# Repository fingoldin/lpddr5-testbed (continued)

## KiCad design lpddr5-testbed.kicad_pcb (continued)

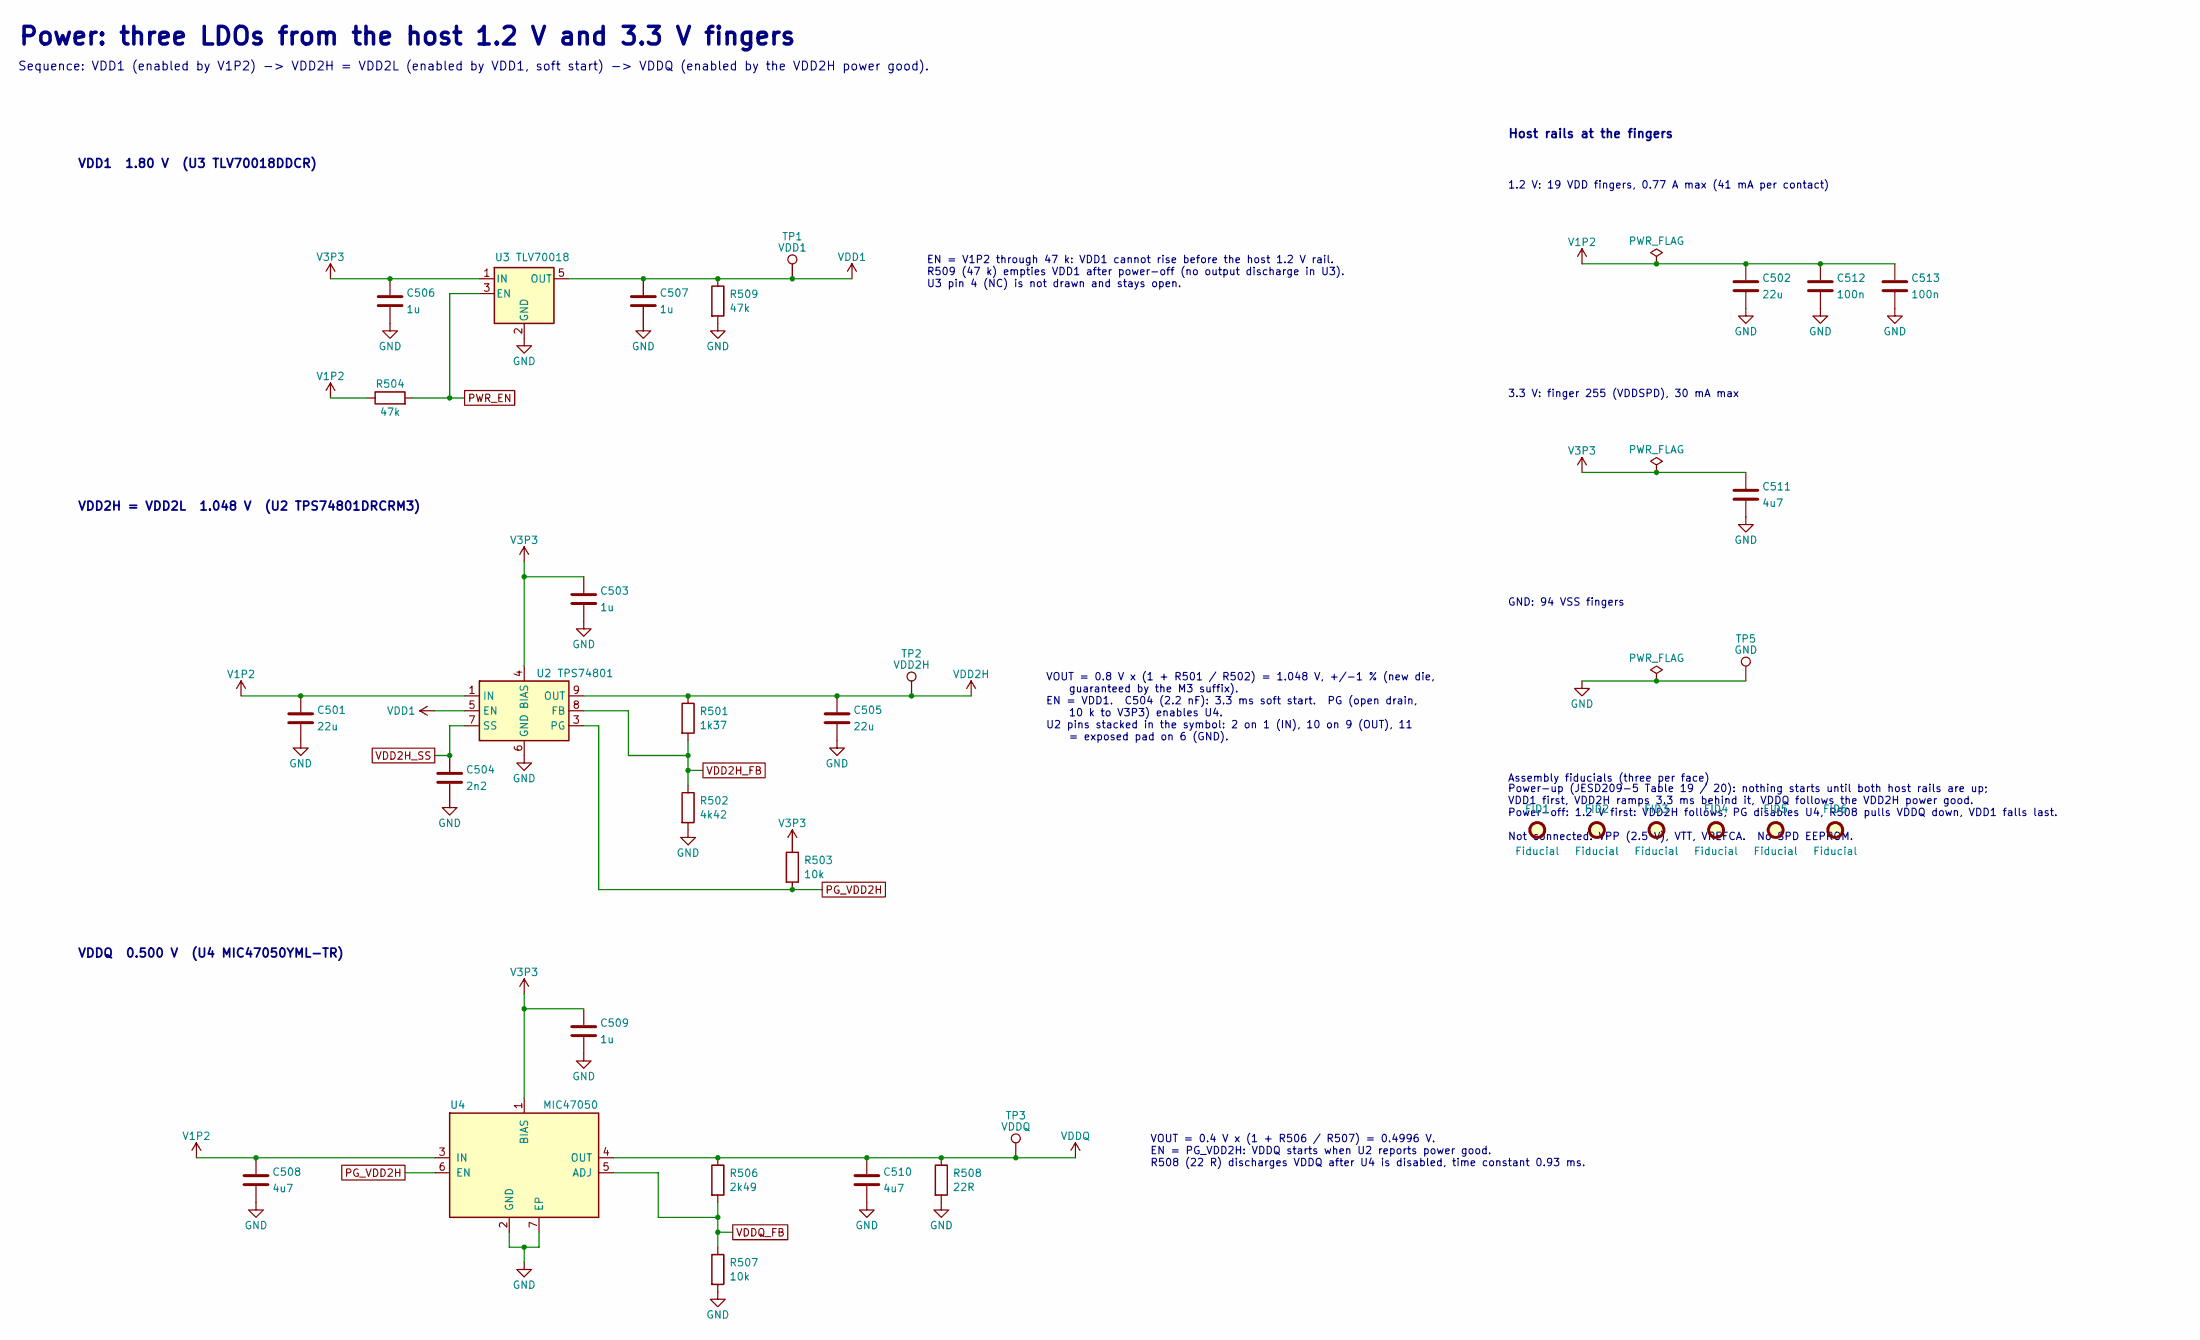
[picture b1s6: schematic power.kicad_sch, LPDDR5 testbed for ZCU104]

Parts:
C501, C502, C505: 22u; C_0603_1608Metric; MPN CL10A226MQ8NRNC
C503, C506, C507, C509: 1u; C_0402_1005Metric; MPN CL05A105KP5NNNC
C504: 2n2; C_0402_1005Metric; MPN CL05B222KB5NNNC
C508, C510, C511: 4u7; C_0402_1005Metric; MPN CL05A475MP5NRNC
C512, C513: 100n; C_0402_1005Metric; MPN CL05B104KO5NNNC
FID1, FID2, FID3, FID4, FID5, FID6: Fiducial; Fiducial_1mm_Mask2mm; MPN N/A (PCB feature)
R501: 1k37; R_0402_1005Metric; MPN RC0402FR-071K37L
R502: 4k42; R_0402_1005Metric; MPN RC0402FR-074K42L
R503, R507: 10k; R_0402_1005Metric; MPN RC0402FR-0710KL
R504, R509: 47k; R_0402_1005Metric; MPN RC0402FR-0747KL
R506: 2k49; R_0402_1005Metric; MPN RC0402FR-072K49L
R508: 22R; R_0201_0603Metric; MPN RC0201FR-0722RL
TP1: VDD1; TestPoint_Pad_D1.0mm; MPN N/A (PCB pad)
TP2: VDD2H; TestPoint_Pad_D1.0mm; MPN N/A (PCB pad)
TP3: VDDQ; TestPoint_Pad_D1.0mm; MPN N/A (PCB pad)
TP5: GND; TestPoint_Pad_D1.0mm; MPN N/A (PCB pad)
U2: TPS74801; VSON-10-1EP_3x3mm_P0.5mm_EP1.65x2.4mm; MPN TPS74801DRCRM3
U3: TLV70018; TSOT-23-5; MPN TLV70018DDCR
U4: MIC47050; MLF-6-1EP_2x2mm_P0.65mm_EP0.8x1.4mm; MPN MIC47050YML-TR

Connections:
GND: C501.2, C502.2, C503.2, C504.2, C505.2, C506.2, C507.2, C508.2, C509.2, C510.2, C511.2, C512.2, C513.2, R502.2, R507.2, R508.2, R509.2, TP5.1, U2.6 (GND), U2.11 (GND), U3.2 (GND), U4.2 (GND), U4.7 (EP); also elsewhere on the board
PG_VDD2H: R503.2, U2.3 (PG), U4.6 (EN)
PWR_EN: R504.2, U3.3 (EN)
V1P2: C501.1, C502.1, C508.1, C512.1, C513.1, R504.1, U2.1 (IN), U2.2 (IN), U4.3 (IN); also elsewhere on the board
V3P3: C503.1, C506.1, C509.1, C511.1, R503.1, U2.4 (BIAS), U3.1 (IN), U4.1 (BIAS); also elsewhere on the board
VDD1: C507.1, R509.1, TP1.1, U2.5 (EN), U3.5 (OUT); also elsewhere on the board
VDD2H: C505.1, R501.1, TP2.1, U2.9 (OUT), U2.10 (OUT); also elsewhere on the board
VDD2H_FB: R501.2, R502.1, U2.8 (FB)
VDD2H_SS: C504.1, U2.7 (SS)
VDDQ: C510.1, R506.1, R508.1, TP3.1, U4.4 (OUT); also elsewhere on the board
VDDQ_FB: R506.2, R507.1, U4.5 (ADJ)

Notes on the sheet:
3.3 V: finger 255 (VDDSPD), 30 mA max
VDDQ 0.500 V (U4 MIC47050YML-TR)
1.2 V: 19 VDD fingers, 0.77 A max (41 mA per contact)
Assembly fiducials (three per face)
GND: 94 VSS fingers
VDD1 1.80 V (U3 TLV70018DDCR)
Power-up (JESD209-5 Table 19 / 20): nothing starts until both host rails are up; VDD1 first, VDD2H ramps 3.3 ms behind it, VDDQ follows the VDD2H power good. Power-off: 1.2 V first: VDD2H follows, PG disables U4, R508 pulls VDDQ down, VDD1 falls last. Not connected: VPP (2.5 V), VTT, VREFCA. No SPD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
Sequence: VDD1 (enabled by V1P2) -> VDD2H = VDD2L (enabled by VDD1, soft start) -> VDDQ (enabled by the VDD2H power good).
VOUT = 0.4 V x (1 + R506 / R507) = 0.4996 V. EN = PG_VDD2H: VDDQ starts when U2 reports power good. R508 (22 R) discharges VDDQ after U4 is disabled, time constant 0.93 ms.
VDD2H = VDD2L 1.048 V (U2 TPS74801DRCRM3)
VOUT = 0.8 V x (1 + R501 / R502) = 1.048 V, +/-1 % (new die, guaranteed by the M3 suffix). EN = VDD1. C504 (2.2 nF): 3.3 ms soft start. PG (open drain, 10 k to V3P3) enables U4. U2 pins stacked in the symbol: 2 on 1 (IN), 10 on 9 (OUT), 11 = exposed pad on 6 (GND).
EN = V1P2 through 47 k: VDD1 cannot rise before the host 1.2 V rail. R509 (47 k) empties VDD1 after power-off (no output discharge in U3). U3 pin 4 (NC) is not drawn and stays open.
Power: three LDOs from the host 1.2 V and 3.3 V fingers
Host rails at the fingers

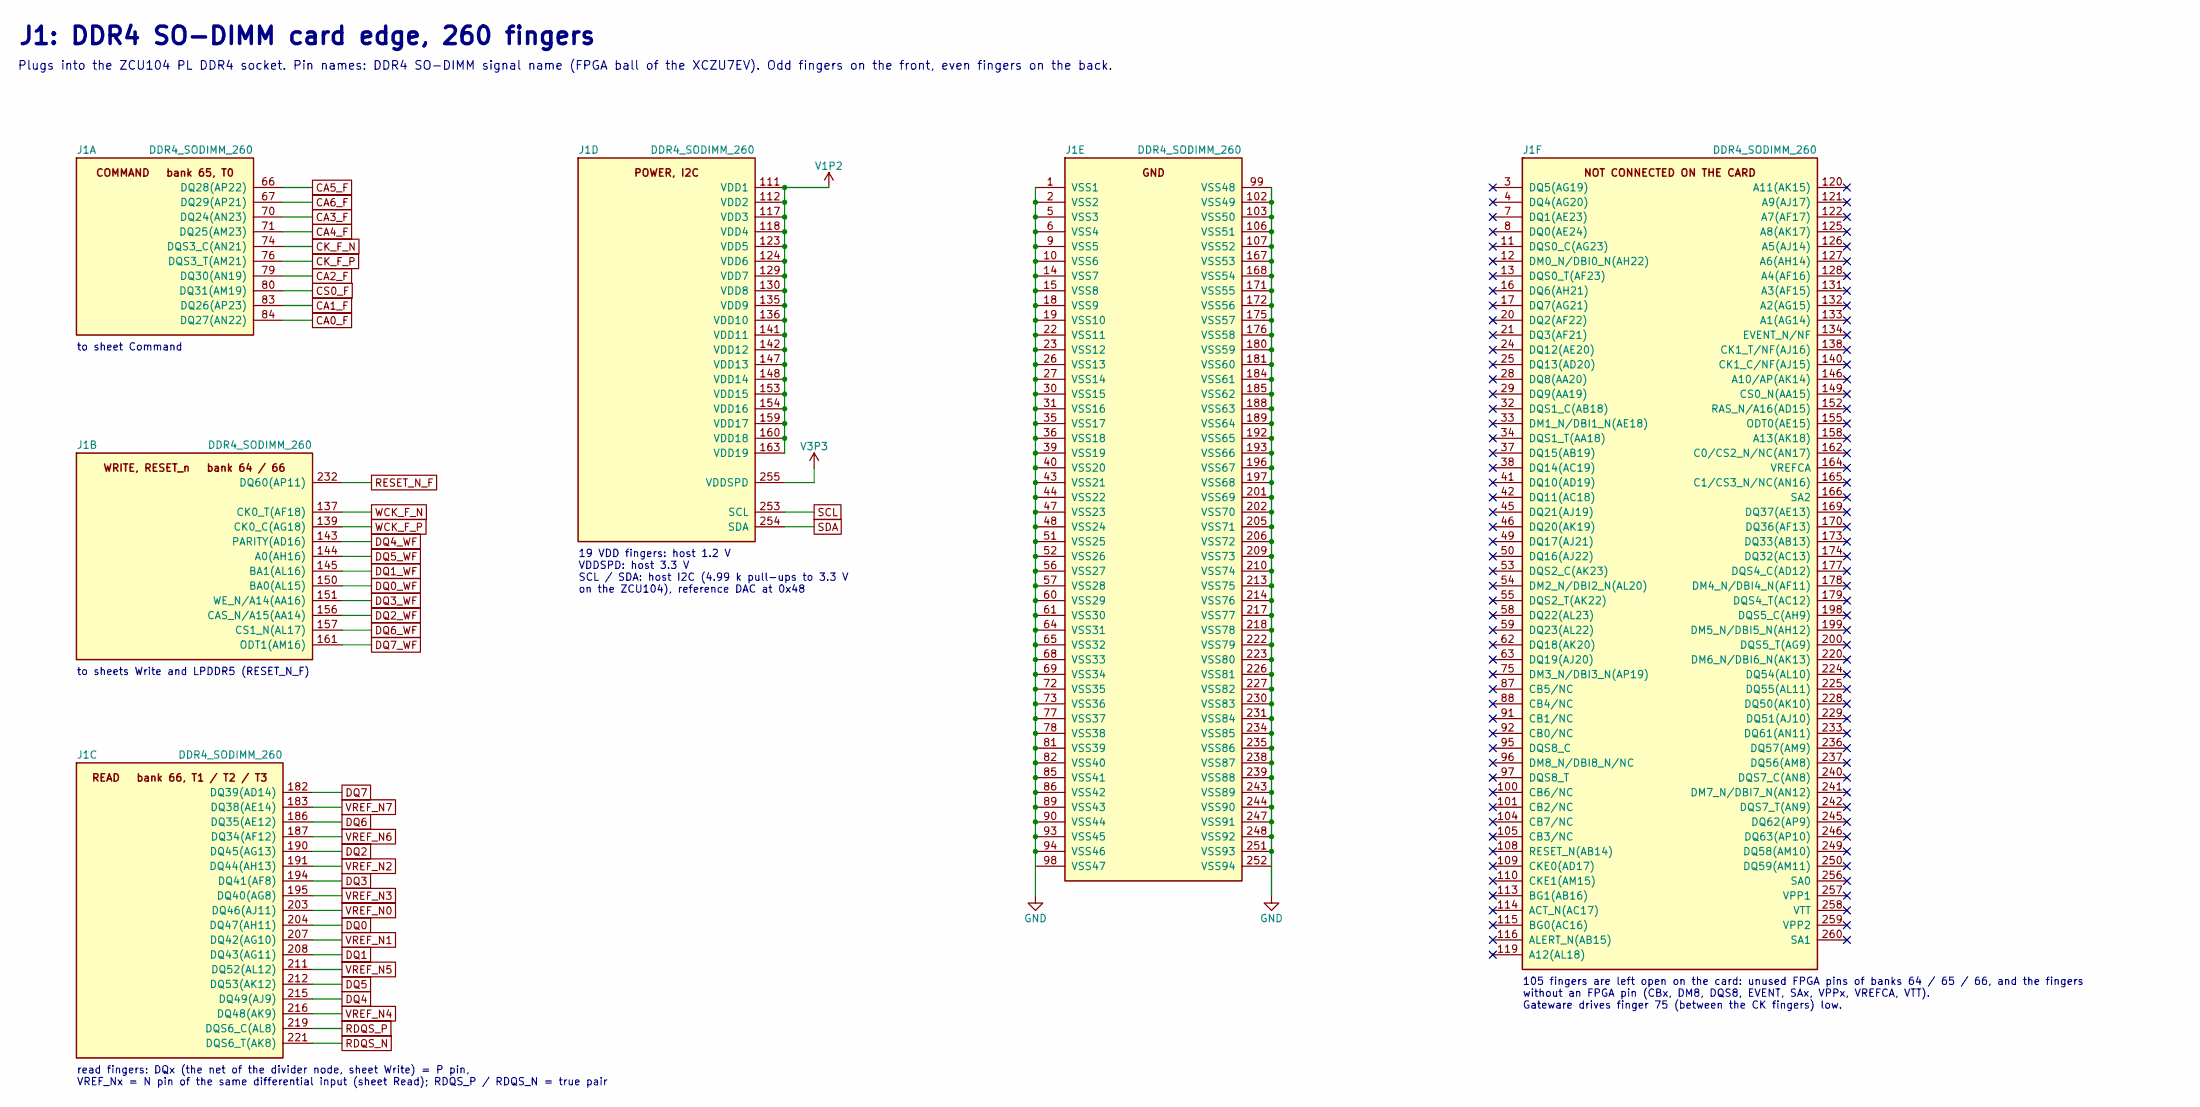
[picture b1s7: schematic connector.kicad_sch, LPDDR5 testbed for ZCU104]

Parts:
J1: DDR4_SODIMM_260; DDR4_SODIMM_260_Edge; MPN N/A (card edge, hard-gold fingers)

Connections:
CA0_F: J1.84 (DQ27(AN22)); also elsewhere on the board
CA1_F: J1.83 (DQ26(AP23)); also elsewhere on the board
CA2_F: J1.79 (DQ30(AN19)); also elsewhere on the board
CA3_F: J1.70 (DQ24(AN23)); also elsewhere on the board
CA4_F: J1.71 (DQ25(AM23)); also elsewhere on the board
CA5_F: J1.66 (DQ28(AP22)); also elsewhere on the board
CA6_F: J1.67 (DQ29(AP21)); also elsewhere on the board
CK_F_N: J1.74 (DQS3_C(AN21)); also elsewhere on the board
CK_F_P: J1.76 (DQS3_T(AM21)); also elsewhere on the board
CS0_F: J1.80 (DQ31(AM19)); also elsewhere on the board
DQ0: J1.204 (DQ47(AH11)); also elsewhere on the board
DQ0_WF: J1.150 (BA0(AL15)); also elsewhere on the board
DQ1: J1.208 (DQ43(AG11)); also elsewhere on the board
DQ1_WF: J1.145 (BA1(AL16)); also elsewhere on the board
DQ2: J1.190 (DQ45(AG13)); also elsewhere on the board
DQ2_WF: J1.156 (CAS_N/A15(AA14)); also elsewhere on the board
DQ3: J1.194 (DQ41(AF8)); also elsewhere on the board
DQ3_WF: J1.151 (WE_N/A14(AA16)); also elsewhere on the board
DQ4: J1.215 (DQ49(AJ9)); also elsewhere on the board
DQ4_WF: J1.143 (PARITY(AD16)); also elsewhere on the board
DQ5: J1.212 (DQ53(AK12)); also elsewhere on the board
DQ5_WF: J1.144 (A0(AH16)); also elsewhere on the board
DQ6: J1.186 (DQ35(AE12)); also elsewhere on the board
DQ6_WF: J1.157 (CS1_N(AL17)); also elsewhere on the board
DQ7: J1.182 (DQ39(AD14)); also elsewhere on the board
DQ7_WF: J1.161 (ODT1(AM16)); also elsewhere on the board
GND: J1.1 (VSS1), J1.2 (VSS2), J1.5 (VSS3), J1.6 (VSS4), J1.9 (VSS5), J1.10 (VSS6), J1.14 (VSS7), J1.15 (VSS8), J1.18 (VSS9), J1.19 (VSS10), J1.22 (VSS11), J1.23 (VSS12), J1.26 (VSS13), J1.27 (VSS14), J1.30 (VSS15), J1.31 (VSS16), J1.35 (VSS17), J1.36 (VSS18), J1.39 (VSS19), J1.40 (VSS20), J1.43 (VSS21), J1.44 (VSS22), J1.47 (VSS23), J1.48 (VSS24), J1.51 (VSS25), J1.52 (VSS26), J1.56 (VSS27), J1.57 (VSS28), J1.60 (VSS29), J1.61 (VSS30), J1.64 (VSS31), J1.65 (VSS32), J1.68 (VSS33), J1.69 (VSS34), J1.72 (VSS35), J1.73 (VSS36), J1.77 (VSS37), J1.78 (VSS38), J1.81 (VSS39), J1.82 (VSS40), J1.85 (VSS41), J1.86 (VSS42), J1.89 (VSS43), J1.90 (VSS44), J1.93 (VSS45), J1.94 (VSS46), J1.98 (VSS47), J1.99 (VSS48), J1.102 (VSS49), J1.103 (VSS50), J1.106 (VSS51), J1.107 (VSS52), J1.167 (VSS53), J1.168 (VSS54), J1.171 (VSS55), J1.172 (VSS56), J1.175 (VSS57), J1.176 (VSS58), J1.180 (VSS59), J1.181 (VSS60), J1.184 (VSS61), J1.185 (VSS62), J1.188 (VSS63), J1.189 (VSS64), J1.192 (VSS65), J1.193 (VSS66), J1.196 (VSS67), J1.197 (VSS68), J1.201 (VSS69), J1.202 (VSS70), J1.205 (VSS71), J1.206 (VSS72), J1.209 (VSS73), J1.210 (VSS74), J1.213 (VSS75), J1.214 (VSS76), J1.217 (VSS77), J1.218 (VSS78), J1.222 (VSS79), J1.223 (VSS80)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; also elsewhere on the board
RDQS_N: J1.221 (DQS6_T(AK8)); also elsewhere on the board
RDQS_P: J1.219 (DQS6_C(AL8)); also elsewhere on the board
RESET_N_F: J1.232 (DQ60(AP11)); also elsewhere on the board
SCL: J1.253 (SCL); also elsewhere on the board
SDA: J1.254 (SDA); also elsewhere on the board
V1P2: J1.111 (VDD1), J1.112 (VDD2), J1.117 (VDD3), J1.118 (VDD4), J1.123 (VDD5), J1.124 (VDD6), J1.129 (VDD7), J1.130 (VDD8), J1.135 (VDD9), J1.136 (VDD10), J1.141 (VDD11), J1.142 (VDD12), J1.147 (VDD13), J1.148 (VDD14), J1.153 (VDD15), J1.154 (VDD16), J1.159 (VDD17), J1.160 (VDD18), J1.163 (VDD19); also elsewhere on the board
V3P3: J1.255 (VDDSPD); also elsewhere on the board
VREF_N0: J1.203 (DQ46(AJ11)); also elsewhere on the board
VREF_N1: J1.207 (DQ42(AG10)); also elsewhere on the board
VREF_N2: J1.191 (DQ44(AH13)); also elsewhere on the board
VREF_N3: J1.195 (DQ40(AG8)); also elsewhere on the board
VREF_N4: J1.216 (DQ48(AK9)); also elsewhere on the board
VREF_N5: J1.211 (DQ52(AL12)); also elsewhere on the board
VREF_N6: J1.187 (DQ34(AF12)); also elsewhere on the board
VREF_N7: J1.183 (DQ38(AE14)); also elsewhere on the board
WCK_F_N: J1.137 (CK0_T(AF18)); also elsewhere on the board
WCK_F_P: J1.139 (CK0_C(AG18)); also elsewhere on the board

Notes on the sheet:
to sheet Command
105 fingers are left open on the card: unused FPGA pins of banks 64 / 65 / 66, and the fingers without an FPGA pin (CBx, DM8, DQS8, EVENT, SAx, VPPx, VREFCA, VTT). Gateware drives finger 75 (between the CK fingers) low.
read fingers: DQx (the net of the divider node, sheet Write) = P pin, VREF_Nx = N pin of the same differential input (sheet Read); RDQS_P / RDQS_N = true pair
19 VDD fingers: host 1.2 V VDDSPD: host 3.3 V SCL / SDA: host I2C (4.99 k pull-ups to 3.3 V on the ZCU104), reference DAC at 0x48
to sheets Write and LPDDR5 (RESET_N_F)
Plugs into the ZCU104 PL DDR4 socket. Pin names: DDR4 SO-DIMM signal name (FPGA ball of the XCZU7EV). Odd fingers on the front, even fingers on the back.
J1: DDR4 SO-DIMM card edge, 260 fingers

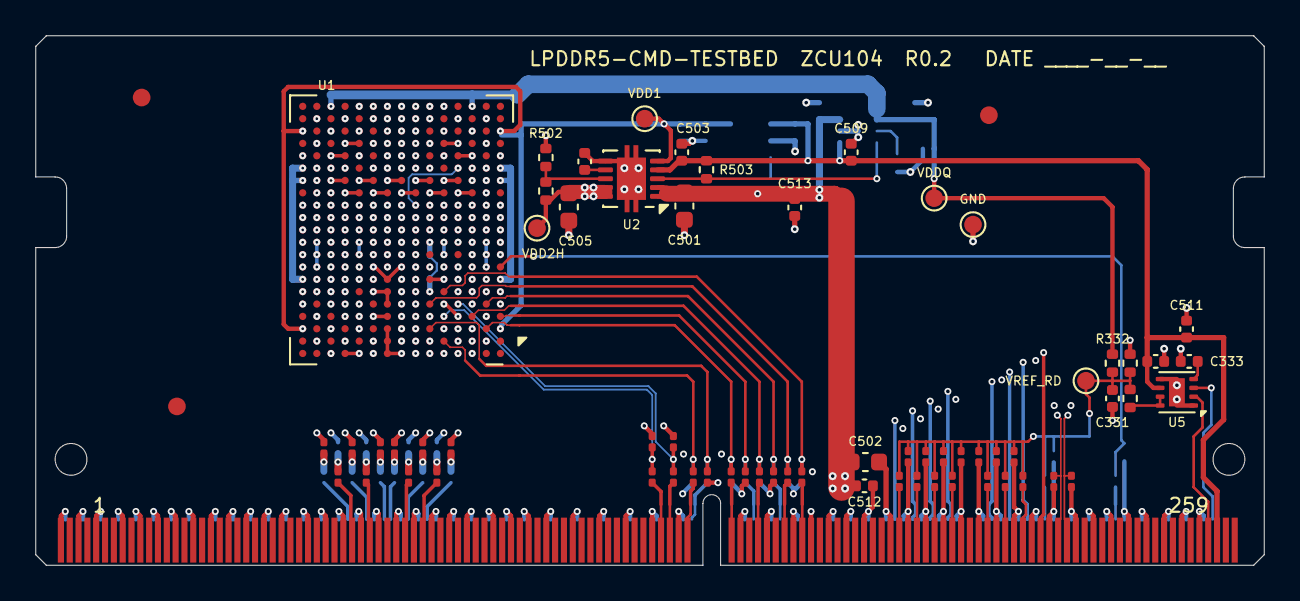
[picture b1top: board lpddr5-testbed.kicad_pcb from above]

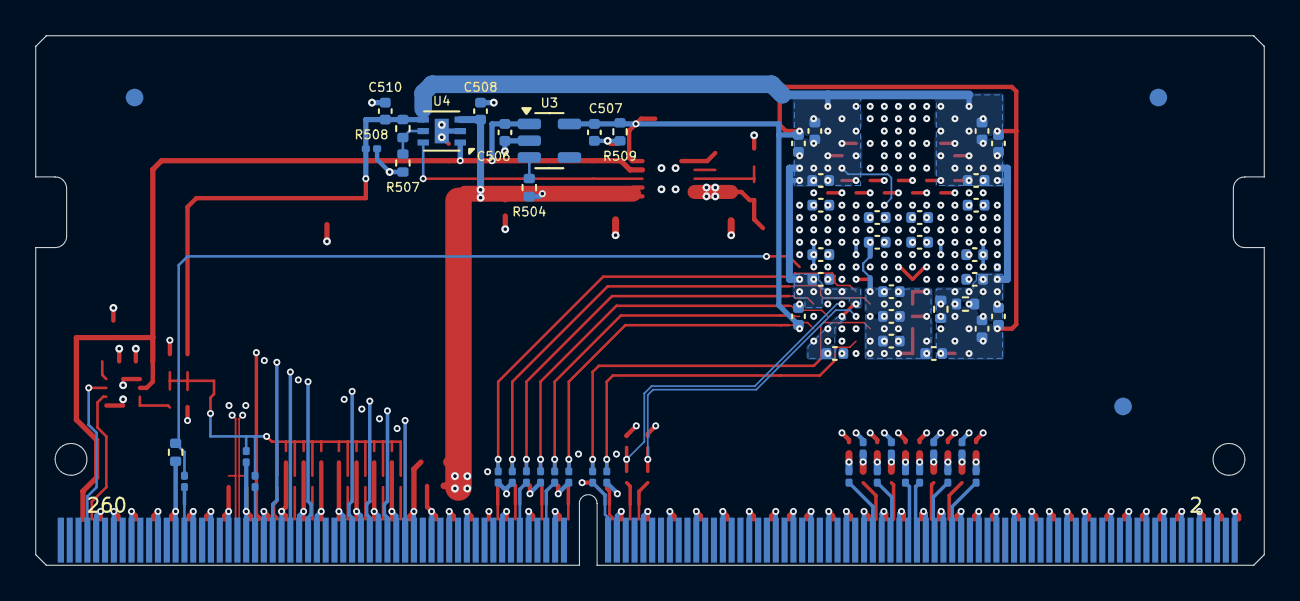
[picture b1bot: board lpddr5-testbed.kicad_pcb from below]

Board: 6 copper layers, 69.6 x 30.0 mm, 131 parts (63 on the bottom side), 71 nets.

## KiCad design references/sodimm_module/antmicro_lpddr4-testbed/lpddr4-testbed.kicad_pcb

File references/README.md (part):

# References

Documents and models used to design and verify the LPDDR5 testbed (developed as internal rev 2.x, released as rev 1.0.0 / 1.1.0), copied here for future work.
Vendor PCB-design guidelines collected afterwards are indexed in `vendor_index.json` and reviewed in `VENDOR_GUIDELINES_REVIEW.md`
(folders `amd/`, `micron/`; the empty `other/` was removed). Every PDF has a `.txt` extract where one was made, for grep. Zip archives are git-ignored.

| File | Document | Used for | Source |
|---|---|---|---|
| `jedec/JESD209-5C_LPDDR5.txt` | JEDEC JESD209-5C LPDDR5 standard (text extract of a purchased copy; licence: single user, do not redistribute outside the team) | Power-up/down order (Tables 19/22), overshoot (Table 416), Rx masks (Tables 466/467), tCK range, tWCK2DQI/O drift (Table 462); U1 ball map (16.3.2, 315-ball 2CHx32, MO-338A), single-rail VDD2 / MR13 OP[7] (4.1.2), ZQ 240 ohm (4.2.1.5), RESET_n levels (Table 414) | purchased |
| `fpga/UG571_UltraScale_SelectIO.pdf` | AMD UG571 UltraScale SelectIO Resources | Native-mode bitslices, VAR_LOAD delays, EN_VTC, DCI | https://docs.amd.com/r/en-US/ug571-ultrascale-selectio |
| `zcu104/UG1267_ZCU104_user_guide_v1.1.pdf` | AMD UG1267 ZCU104 Evaluation Board User Guide v1.1 | SO-DIMM socket, clocks, bank voltages | https://docs.amd.com/v/u/en-US/ug1267-zcu104-eval-bd |
| `zcu104/XTP484_ZCU104_schematic_rev1.0.pdf` | ZCU104 rev 1.0 schematic (XTP484) | Host connections of every SO-DIMM finger, PUDC_B, 1.2 V rail (IRPS5401) | https://www.xilinx.com/member/forms/download/design-license.html?filename=zcu104-schematic-xtp484.zip |
| `zcu104/XTP485_ZCU104_layout_rev1.0.pdf` | ZCU104 rev 1.0 Allegro layout plots (XTP485) | Host trace geometry | https://docs.amd.com/v/u/en-US/ZCU104-Allegro-Board-XTP485 |
| `zcu104/RDF0439_ZCU104_allegro_board_source.zip` | ZCU104 Allegro board source (RDF0439, binary .brd, git-ignored zip) | Not machine-read (needs Allegro); kept for reference | AMD ZCU104 design files page |
| `zcu104/odb/8955_1280961_hw-z1-zcu104_revision-1_0_odb.tgz` | ZCU104 rev 1.0 layout as ODB++ (from the RDF0440 Gerber package, `odb++/` folder; git-ignored) | Host trace sections for the SI model: `scripts/zcu104_board_extract.py` -> `sim/si/results/zcu104_host_paths.json` (method: `doc/ZCU104_BOARD_DATA.md`) | AMD ZCU104 design files page (RDF0440 Gerber files) |
| `zcu104/RDF0437_ZCU104_BOM_rev1.0.pdf` | ZCU104 rev 1.0 BOM | Host regulators and socket part | AMD ZCU104 design files page |
| `zcu104/ZCU104_stackup_Whizz8955.txt` | ZCU104 stackup (text extract from the Gerber package) | Host trace impedance and delay | AMD ZCU104 Gerber package |
| `zcu104/IRPS5401_PMIC_datasheet.pdf` | Infineon IRPS5401 PMIC data sheet | Host 1.2 V rail tolerance for the U21 dropout check | https://www.infineon.com/dgdl/irps5401.pdf |
| `dram/Micron_Y42M_LPDDR5X_315b_441b_563b_RevF.pdf` | Micron Y42M LPDDR5X addendum Rev. F (Digi-Key mirror) | CS/DQ Rx masks, IDD tables, 315-ball maps | https://mm.digikey.com/Volume0/opasdata/d220001/medias/docus/6592/315b441b563by42msdpddpqdp8dplpddr5xitwt.pdf |
| `dram/Micron_Y31M_LPDDR5_multi_package.pdf` | Micron Y31M LPDDR5 multi-package addendum | MT62F1G32D4DR pin-compatibility (315 balls), IDD | https://mm.digikey.com/Volume0/opasdata/d220001/medias/docus/8885/441b-315b-y31m-lpddr5-multi-pkg.pdf |
| `dram/Micron_MT62F_315b_Y31M.pdf` | Micron MT62F 315-ball Y31M addendum | Ball map, package | Digi-Key / Micron |
| `dram/Micron_315b_LPDDR5X_ballout.pdf` | Micron Y52Q LPDDR5X data sheet (MT62F512M32D1 / MT62F512M64D2; 315-, 441-, 496- and 561-ball maps) | Ball-map cross-check (Figure 7, 315-ball dual-channel) | Micron |
| `dram/Micron_315b_ballmap.png` | Micron 315-ball map render | Visual pin-1/ball check | derived |
| `dram/SKhynix_LPDDR5_candidate_datasheet.pdf` | SK hynix 12 GB LPDDR5 496-ball PoP specification (Oct 2020; not the U1 part), with the JEDEC LPDDR5 text reproduced | Supplies; its copy of the JEDEC 315-ball 2CHx32 ballout (16.3.2, p. 573: matches JEDEC, but the row letters skip U and add AB). The exact H9JCNNNCP3MLYR-N6E sheet is not public | web |
| `dram/Rayson_RS1G64LP5_LPDDR5X_496b_PoP.pdf` | Rayson RS1G64LP5 LPDDR5X data sheet (496-ball quad-channel PoP; the file was earlier misnamed 315b) | Third-party ball names only; not a U1 (315-ball) reference | LCSC |
| `dram/Acer_service_manual_memory_AVL_extract.txt` | Acer service manual (text): lists Hynix H9JCNNNCP3MLYR-N6E and Micron MT62F1G32D4DR-031 WT:B as alternatives | Evidence for the Micron alternative | https://documents.cdn.ifixit.com/aqAP5mMubp5dfyFf.pdf |
| `parts/TI_TPS74801.pdf` | TI TPS74801 LDO | U21 VDD2H (and U20 VDD1 until 2026-10-17): accuracy, dropout, sequencing | https://www.ti.com/lit/ds/symlink/tps748.pdf |
| `parts/TI_TPS74701.pdf` (+ .txt) | TI TPS74701 LDO, SBVS099H | U20 VDD1 since 2026-10-17 (`validation/eco_20261017_u20_tps74701.json`) | https://www.ti.com/lit/ds/symlink/tps74701.pdf |
| `parts/TI_TPS7A84A.pdf` | TI TPS7A84A LDO | U22 VDDQ 0.5 V | https://www.ti.com/lit/ds/symlink/tps7a84a.pdf |
| `parts/TI_SN74AXC1T45.pdf` | TI SN74AXC1T45 level shifter | U23 PWR_EN 1.2 V -> 3.3 V | https://www.ti.com/lit/ds/symlink/sn74axc1t45.pdf |
| `parts/TI_DAC53401.pdf` | TI DAC53401 DAC | U11 VREF_RD | https://www.ti.com/lit/ds/symlink/dac53401.pdf |
| `parts/TI_TMP117.pdf` | TI TMP117 temperature sensor | U10 (thermal pad left unsoldered, 10.1) | https://www.ti.com/lit/ds/symlink/tmp117.pdf |
| `parts/Samsung_CL05A_X5R_series.pdf` | Samsung CL05A MLCC series | DC-bias derating of the 0402 X5R parts | Samsung EM |
| `parts/Samsung_CL05A475MP5NRNC_dcbias.json` | Samsung CL05A475MP5NRNC DC-bias curve data | C90 / 4.7 uF derating | Samsung EM part page |
| `parts/Samsung_CL05A225KP5NSNC.pdf` | Samsung CL05A225KP5NSNC | C99 | Samsung EM |
| `parts/UniRoyal_0402WGF.pdf` | UNI-ROYAL 0402 thick-film resistors | Resistor tolerance/TCR | LCSC |
| `parts/UniRoyal_4D02_array.pdf` | UNI-ROYAL 4D02 resistor arrays | Shunt arrays | LCSC |
| `parts/Bourns_CR0402.pdf` | Bourns CR0402 resistors | R125-R127 etc. | Bourns |
| `socket/Foxconn_DDR4_SODIMM_socket.pdf` | Foxconn DDR4 SO-DIMM socket drawing | Card thickness 1.10-1.30 mm, keep-outs, key | https://wmsc.lcsc.com/wmsc/upload/file/pdf/v2/lcsc/FOXCONN-AS0A821-H4SB-7H_C225720.pdf |
| `socket/DDR4_SODIMM_socket_comet28777.pdf` | DDR4 SO-DIMM socket drawing (second vendor) | Mechanical cross-check | web |
| `models/tps7a84/` | TI TPS7A84 PSpice transient model | Power-sequencing sims of U22 | https://www.ti.com/product/TPS7A84A#design-tools-simulation |
| `models/dram/` | LPDDR4X IBIS proxies (Alliance, Winbond) and the Versal LVSTL extract, with URLs in its README | DRAM driver/package proxy model (`doc/DRAM_MODEL.md`) | see `models/dram/README.md` |
| `models/zynquplus_ibis_extract/` | Zynq UltraScale+ IBIS models used by the SI flow (extracted from Vivado 2023.1 data/parts/xilinx/zynquplus/public/ibis/zynquplus.ibs, 124 MB) | FPGA drivers/receivers: HP_SSTL12/POD12 40/48/60, MIPI_DPHY_DCI, LVCMOS12 | Vivado install |

Not public (needs a my.micron.com account or an NDA): Micron "General LPDDR5/LPDDR5X Specifications 2: AC/DC and
Interface Specifications" and the MT62F1G32D4DR / Y31M HSPICE/IBIS models; the exact SK hynix H9JCNNNCP3MLYR-N6E data
sheet and models. Data sheets of the 2026-10-17 U1 parts (LPDDR5X H58G56BK7BX068N, K3KL8L80CM-MGCT) are not in
`references/` either. The SI flow uses an inferred DRAM model instead (sim/si/tools/cases.py DRAM_DRV, chan.py parasitics;
since 2026-10-13 the proxy model in `sim/si/dram_model/`, `doc/DRAM_MODEL.md`).

## Reviews against external guidance

| Folder | Contents | Review |
|---|---|---|
| `amd/`, `micron/` | AMD UG583, UG571, DS925, PG188, PG150, UG1075, XAPP1274/1330, ...; Micron BGA/soldering/thermal notes, MT62F short sheet | `VENDOR_GUIDELINES_REVIEW.md`, `vendor_index.json` |
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
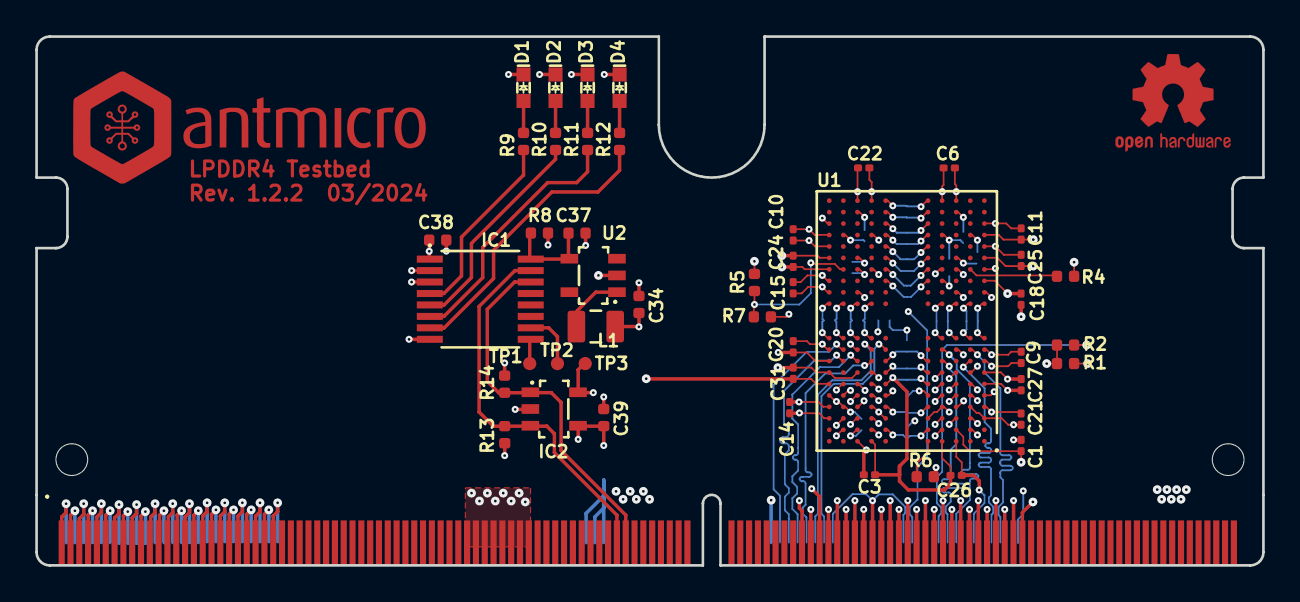
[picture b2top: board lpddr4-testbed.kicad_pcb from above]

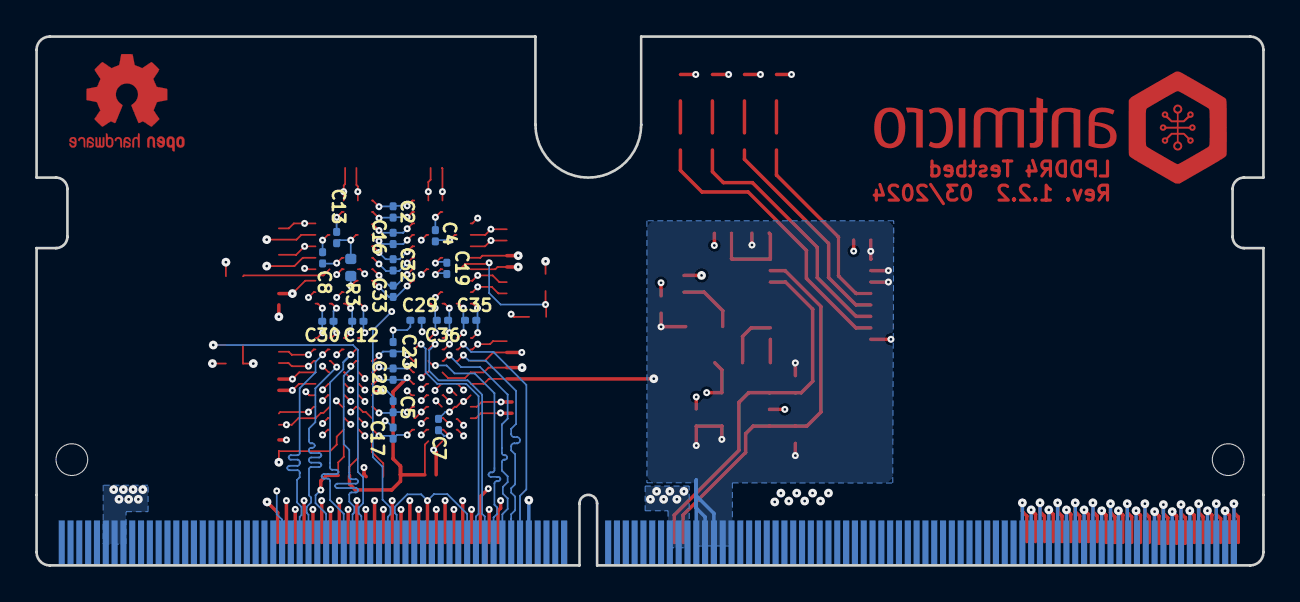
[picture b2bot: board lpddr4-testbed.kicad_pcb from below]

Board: 6 copper layers, 69.6 x 30.0 mm, 66 parts (19 on the bottom side), 57 nets.

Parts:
C1, C2, C3, C4, C5, C6, C7, C8, C9, C10, C11, C12, C13, C14, C15, C16, C17, C18, C19, C20, C21, C22, C23, C24, C25, C26, C27, C28, C29, C30, C31, C32, C33, C35, C36: C_100n_0201; C_0201
C34, C37: C_4u7_0402; C_0402_1005Metric
C38, C39: C_100n_0402; C_0402_1005Metric
D1, D2, D3, D4: LED_G_0603_KP-1608CGCK; LED_0603_1608Metric_G
IC1: PCA6408A_TSSOP; TSSOP-16_4.4x5mm_P0.65mm
IC2: AT24CS01_SOT23; SOT-23-5
J1: Bus_DDR4_Edge_Conn; Edge_Conn_Bus_DDR4
L1: L_2u2_1.5A_1285AS-H; L_0806_2016Metric
R1, R3, R4, R5, R13, R14: R_10k_0402; R_0402_1005Metric
R2, R7, R8: R_0R_0402; R_0402_1005Metric
R6: R_240R_0402; R_0402_1005Metric
R9, R10, R11, R12: R_220R_0402; R_0402_1005Metric
TP1, TP2, TP3: TP_0.75mm_SMD; TP_SMD_0.75mm
U1: MT53E1G32D2NP-046; BGA-264-200_10x14.5mm_Layout12x22_P0.8x0.65mm
U2: TPS613221A_SOT-23-5; SOT-23-5

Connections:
CA0_A: J1.204, U1.H2 (CA0_A)
CA1_A: J1.206, U1.J2 (CA1_A)
CA2_A: J1.162, U1.H9 (CA2_A)
CA3_A: J1.160, U1.H10 (CA3_A)
CA4_A: J1.158, U1.H11 (CA4_A)
CA5_A: J1.156, U1.J11 (CA5_A)
CKE0_A: J1.196, U1.J4 (CKE0_A)
CK_C_A: J1.164, U1.J9 (CK_C_A)
CK_T_A: J1.166, U1.J8 (CK_T_A)
CS0_A: J1.194, U1.H4 (CS0_A)
CS0_B: R3.1, U1.R4 (CS0_B)
DMI_0A: J1.197, U1.C3 (DMI0_A)
DMI_1A: J1.171, U1.C10 (DMI1_A)
DQ00_A: J1.203, U1.B2 (DQ0_A)
DQ01_A: J1.205, U1.C2 (DQ1_A)
DQ02_A: J1.207, U1.E2 (DQ2_A)
DQ03_A: J1.209, U1.F2 (DQ3_A)
DQ04_A: J1.187, U1.F4 (DQ4_A)
DQ05_A: J1.189, U1.E4 (DQ5_A)
DQ06_A: J1.191, U1.C4 (DQ6_A)
DQ07_A: J1.193, U1.B4 (DQ7_A)
DQ08_A: J1.169, U1.B11 (DQ8_A)
DQ09_A: J1.167, U1.C11 (DQ9_A)
DQ10_A: J1.165, U1.E11 (DQ10_A)
DQ11_A: J1.163, U1.F11 (DQ11_A)
DQ12_A: J1.185, U1.F9 (DQ12_A)
DQ13_A: J1.183, U1.E9 (DQ13_A)
DQ14_A: J1.181, U1.C9 (DQ14_A)
DQ15_A: J1.179, U1.B9 (DQ15_A)
DQ_S0_CA: J1.199, U1.E3 (DQS0_C_A)
DQ_S0_TA: J1.201, U1.D3 (DQS0_T_A)
DQ_S1_CA: J1.173, U1.E10 (DQS1_C_A)
DQ_S1_TA: J1.175, U1.D10 (DQS1_T_A)
GND: C1.1, C2.1, C3.1, C4.1, C5.1, C6.1, C7.1, C8.1, C9.1, C10.1, C11.1, C12.1, C13.1, C14.1, C15.1, C16.1, C17.1, C18.1, C19.1, C20.1, C21.1, C22.1, C23.1, C24.1, C25.1, C26.1, C27.1, C28.1, C29.1, C30.1, C31.1, C32.1, C33.1, C34.1, C35.1, C36.1, C37.1, C38.1, C39.1, D1.2, D2.2, D3.2, D4.2, IC1.8 (GND), IC2.2 (GND), IC2.5 (WP), J1.1, J1.2, J1.3, J1.4, J1.5, J1.6, J1.7, J1.8, J1.9, J1.10, J1.11, J1.12, J1.13, J1.14, J1.15, J1.16, J1.17, J1.18, J1.19, J1.20, J1.21, J1.22, J1.23, J1.24, J1.25, J1.26, J1.27, J1.28, J1.29, J1.30, J1.31, J1.32, J1.33, J1.34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
unnamed: D1.1, R9.2
unnamed: D2.1, R10.2
unnamed: D3.1, R11.2
unnamed: D4.1, R12.2
unnamed: IC1.4 (P0), R9.1
unnamed: IC1.5 (P1), R10.1
unnamed: IC1.6 (P2), R11.1
unnamed: IC1.7 (P3), R12.1
unnamed: IC1.9 (P4), TP1.1
unnamed: IC1.10 (P5), TP2.1
unnamed: R1.2, R2.1, U1.G2 (ODT_CA_A)
unnamed: R5.2, R7.1, U1.T11 (RESET_N)
unnamed: R6.1, U1.A5 (ZQ0)
unnamed: R4.2, U1.T2 (ODT_CA_B)
unnamed: L1.2, U2.1 (SW)
ODT_CA_A: J1.192, R2.2
RESET_N: J1.186, R7.2
SCL: IC1.14 (SCL), IC2.1 (SCL), J1.129, R14.2
SDA: IC1.15 (SDA), IC2.3 (SDA), J1.127, R13.2
VDD1: C24.2, C25.2, C27.2, C29.2, C31.2, C34.2, C38.2, C39.2, IC1.1 (VDD(I2C)), IC1.2 (ADDR), IC1.3 (~RESET), IC2.4 (VCC), J1.116, J1.118, J1.120, J1.122, J1.124, L1.1, R8.1, R13.1, R14.1, U1.F1 (VDD1), U1.F12 (VDD1), U1.G4 (VDD1), U1.G9 (VDD1), U1.T4 (VDD1), U1.T9 (VDD1), U1.U1 (VDD1), U1.U12 (VDD1)
VDD2: C3.2, C6.2, C9.2, C12.2, C15.2, C18.2, C20.2, C22.2, C23.2, C26.2, C28.2, C30.2, C32.2, C33.2, C35.2, C36.2, J1.93, J1.95, J1.97, J1.99, J1.101, J1.103, J1.105, J1.107, U1.A4 (VDD2), U1.A9 (VDD2), U1.AB4 (VDD2), U1.AB9 (VDD2), U1.F5 (VDD2), U1.F8 (VDD2), U1.H1 (VDD2), U1.H5 (VDD2), U1.H8 (VDD2), U1.H12 (VDD2), U1.K1 (VDD2), U1.K3 (VDD2), U1.K10 (VDD2), U1.K12 (VDD2), U1.N1 (VDD2), U1.N3 (VDD2), U1.N10 (VDD2), U1.N12 (VDD2), U1.R1 (VDD2), U1.R5 (VDD2), U1.R8 (VDD2), U1.R12 (VDD2), U1.U5 (VDD2), U1.U8 (VDD2)
VDDLED: C37.2, IC1.16 (VDD(P)), R8.2, U2.4 (VOUT)
VDDQ: C1.2, C2.2, C4.2, C5.2, C7.2, C8.2, C10.2, C11.2, C13.2, C14.2, C16.2, C17.2, C19.2, C21.2, J1.126, J1.128, J1.130, J1.246, J1.248, J1.250, R1.1, R4.1, R5.1, U1.AA3 (VDDQ), U1.AA5 (VDDQ), U1.AA8 (VDDQ), U1.AA10 (VDDQ), U1.B3 (VDDQ), U1.B5 (VDDQ), U1.B8 (VDDQ), U1.B10 (VDDQ), U1.D1 (VDDQ), U1.D5 (VDDQ), U1.D8 (VDDQ), U1.D12 (VDDQ), U1.F3 (VDDQ), U1.F10 (VDDQ), U1.U3 (VDDQ), U1.U10 (VDDQ), U1.W1 (VDDQ), U1.W5 (VDDQ), U1.W8 (VDDQ), U1.W12 (VDDQ)

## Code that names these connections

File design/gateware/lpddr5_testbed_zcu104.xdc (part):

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## Delay-matched on the card, die pad to ball; CK is not inverted (CK_t on the P pin).
## Source of the standards: design/DESIGN.md section 1 (SSTL12 / DIFF_SSTL12, RDRV_40_40, FAST).
## ------------------------------------------------------------------------------------------------------------
set_property PACKAGE_PIN AN22 [get_ports {ca[0]}]        ;# finger 84 (B) DQ27 | CA0_F -> CA0 (U1.G4) | bank 65 T0U N8 (bitslice 2) | IO_L5P_T0U_N8_AD14P_65 | matched on the card (641.77 ps die pad to ball, +/-2.0 ps)
set_property PACKAGE_PIN AP23 [get_ports {ca[1]}]        ;# finger 83 (F) DQ26 | CA1_F -> CA1 (U1.H5) | bank 65 T0U N9 (bitslice 3) | IO_L5N_T0U_N9_AD14N_65 | matched on the card (641.77 ps die pad to ball, +/-2.0 ps)
set_property PACKAGE_PIN AN19 [get_ports {ca[2]}]        ;# finger 79 (F) DQ30 | CA2_F -> CA2 (U1.G8) | bank 65 T0L N3 (bitslice 3) | IO_L2N_T0L_N3_65 | matched on the card (641.77 ps die pad to ball, +/-2.0 ps)
set_property PACKAGE_PIN AN23 [get_ports {ca[3]}]        ;# finger 70 (B) DQ24 | CA3_F -> CA3 (U1.H11) | bank 65 T0U N11 (bitslice 5) | IO_L6N_T0U_N11_AD6N_65 | matched on the card (641.77 ps die pad to ball, +/-2.0 ps)
set_property PACKAGE_PIN AM23 [get_ports {ca[4]}]        ;# finger 71 (F) DQ25 | CA4_F -> CA4 (U1.G10) | bank 65 T0U N10 (bitslice 4) | IO_L6P_T0U_N10_AD6P_65 | matched on the card (641.77 ps die pad to ball, +/-2.0 ps)
set_property PACKAGE_PIN AP22 [get_ports {ca[5]}]        ;# finger 66 (B) DQ28 | CA5_F -> CA5 (U1.H13) | bank 65 T0L N5 (bitslice 5) | IO_L3N_T0L_N5_AD15N_65 | matched on the card (641.77 ps die pad to ball, +/-2.0 ps)
set_property PACKAGE_PIN AP21 [get_ports {ca[6]}]        ;# finger 67 (F) DQ29 | CA6_F -> CA6 (U1.G12) | bank 65 T0L N4 (bitslice 4) | IO_L3P_T0L_N4_AD15P_65 | matched on the card (641.77 ps die pad to ball, +/-2.0 ps)
set_property PACKAGE_PIN AM21 [get_ports {ck_p}]         ;# finger 76 (B) DQS3_T | CK_F_P -> CK_P (U1.H9) | bank 65 T0U N6 (bitslice 0) DBC | IO_L4P_T0U_N6_DBC_AD7P_SMBALERT_65 | CK_t
set_property PACKAGE_PIN AN21 [get_ports {ck_n}]         ;# finger 74 (B) DQS3_C | CK_F_N -> CK_N (U1.J9) | bank 65 T0U N7 (bitslice 1) DBC | IO_L4N_T0U_N7_DBC_AD7N_65 | CK_c
set_property PACKAGE_PIN AM19 [get_ports {cs0}]          ;# finger 80 (B) DQ31 | CS0_F -> CS0 (U1.H7) | bank 65 T0L N2 (bitslice 2) | IO_L2P_T0L_N2_65 | matched with the CA bus
set_property IOSTANDARD SSTL12 [get_ports {ca[*] cs0}]
set_property OUTPUT_IMPEDANCE RDRV_40_40 [get_ports {ca[*] cs0}]
set_property SLEW FAST [get_ports {ca[*] cs0}]
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## FPGA outputs at 1.2 V into the dividers (DQ 240 + 150 ohm, WCK 91 + 68 ohm).  wdq[*] must be Hi-Z during reads
## (OBUFT): a driven-low write pin costs 36 mV of read level (design/DESIGN.md section 2).
## NOT delay-matched on the card: one ODELAYE3 per pin, values in lpddr5_testbed_pins.vh / PINMAP.md.
## WCK is INVERTED: wck_p (the FPGA P pin) carries WCK_c, wck_n carries WCK_t: drive the pair with inverted data.
## ------------------------------------------------------------------------------------------------------------
set_property PACKAGE_PIN AL15 [get_ports {wdq[0]}]       ;# finger 150 (B) BA0 | DQ0_WF -> DQ0 (U1.D1) | bank 64 T1L N3 (bitslice 3) | IO_L8N_T1L_N3_AD5N_64 | not matched on the card: total 760.77 ps
set_property PACKAGE_PIN AL16 [get_ports {wdq[1]}]       ;# finger 145 (F) BA1 | DQ1_WF -> DQ1 (U1.C2) | bank 64 T1L N2 (bitslice 2) | IO_L8P_T1L_N2_AD5P_64 | not matched on the card: total 750.55 ps
set_property PACKAGE_PIN AA14 [get_ports {wdq[2]}]       ;# finger 156 (B) CAS_N/A15 | DQ2_WF -> DQ2 (U1.E2) | bank 64 T3U N8 (bitslice 2) | IO_L23P_T3U_N8_64 | not matched on the card: total 774.43 ps
set_property PACKAGE_PIN AA16 [get_ports {wdq[3]}]       ;# finger 151 (F) WE_N/A14 | DQ3_WF -> DQ3 (U1.D3) | bank 64 T3U N6 (bitslice 0) DBC | IO_L22P_T3U_N6_DBC_AD0P_64 | not matched on the card: total 760.53 ps
set_property PACKAGE_PIN AD16 [get_ports {wdq[4]}]       ;# finger 143 (F) PARITY | DQ4_WF -> DQ4 (U1.B5) | bank 64 T3U N11 (bitslice 5) | IO_L24N_T3U_N11_64 | not matched on the card: total 748.03 ps
set_property PACKAGE_PIN AH16 [get_ports {wdq[5]}]       ;# finger 144 (B) A0 | DQ5_WF -> DQ5 (U1.C6) | bank 64 T2U N12 (bitslice 6) | IO_T2U_N12_64 | not matched on the card: total 778.44 ps
set_property PACKAGE_PIN AL17 [get_ports {wdq[6]}]       ;# finger 157 (F) CS1_N | DQ6_WF -> DQ6 (U1.E6) | bank 64 T1U N12 (bitslice 6) | IO_T1U_N12_64 | not matched on the card: total 798.09 ps
set_property PACKAGE_PIN AM16 [get_ports {wdq[7]}]       ;# finger 161 (F) ODT1 | DQ7_WF -> DQ7 (U1.F5) | bank 64 T1L N0 (bitslice 0) QBC | IO_L7P_T1L_N0_QBC_AD13P_64 | not matched on the card: total 801.51 ps
set_property PACKAGE_PIN AF18 [get_ports {wck_p}]        ;# finger 137 (F) CK0_T | WCK_F_N -> WCK_N (U1.D5) | bank 64 T2L N2 (bitslice 2) GC | IO_L14P_T2L_N2_GC_64 | WCK_c (PAIR INVERTED on the host: drive inverted)
set_property PACKAGE_PIN AG18 [get_ports {wck_n}]        ;# finger 139 (F) CK0_C | WCK_F_P -> WCK_P (U1.E4) | bank 64 T2L N3 (bitslice 3) GC | IO_L14N_T2L_N3_GC_64 | WCK_t (PAIR INVERTED on the host: drive inverted)
set_property IOSTANDARD SSTL12 [get_ports {wdq[*]}]
set_property OUTPUT_IMPEDANCE RDRV_40_40 [get_ports {wdq[*]}]
set_property SLEW FAST [get_ports {wdq[*]}]
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## DIFF_TERM_ADV TERM_NONE below is the UltraScale+ spelling of DIFF_TERM FALSE: no differential termination,
## because one leg of every data pair is a DC reference.
## NOT delay-matched on the card: one IDELAYE3 per pair, values in lpddr5_testbed_pins.vh / PINMAP.md.
## RDQS is INVERTED: rdqs_p (the FPGA P pin) carries RDQS_c, rdqs_n carries RDQS_t: invert after the receiver.
## Fall-back receiver: read lpddr5_testbed_zcu104_rx_slvs.xdc after this file (SLVS_400_18 on plain IBUFDS).
## ------------------------------------------------------------------------------------------------------------
set_property PACKAGE_PIN AH11 [get_ports {rdq_p[0]}]     ;# finger 204 (B) DQ47 | DQ0 (U1.D1) | bank 66 T2L N2 (bitslice 2) GC | IO_L14P_T2L_N2_GC_66 | not matched on the card: total 896.87 ps, -26.24 ps to the strobe
set_property PACKAGE_PIN AJ11 [get_ports {rdq_n[0]}]     ;# finger 203 (F) DQ46 | VREF_N0 | bank 66 T2L N3 (bitslice 3) GC | IO_L14N_T2L_N3_GC_66 | static reference of rdq_p[0]; never driven by the FPGA
set_property PACKAGE_PIN AG11 [get_ports {rdq_p[1]}]     ;# finger 208 (B) DQ43 | DQ1 (U1.C2) | bank 66 T2U N8 (bitslice 2) | IO_L17P_T2U_N8_AD10P_66 | not matched on the card: total 912.31 ps, -10.81 ps to the strobe
set_property PACKAGE_PIN AG10 [get_ports {rdq_n[1]}]     ;# finger 207 (F) DQ42 | VREF_N1 | bank 66 T2U N9 (bitslice 3) | IO_L17N_T2U_N9_AD10N_66 | static reference of rdq_p[1]; never driven by the FPGA
set_property PACKAGE_PIN AG13 [get_ports {rdq_p[2]}]     ;# finger 190 (B) DQ45 | DQ2 (U1.E2) | bank 66 T2L N4 (bitslice 4) | IO_L15P_T2L_N4_AD11P_66 | not matched on the card: total 861.37 ps, -61.75 ps to the strobe
set_property PACKAGE_PIN AH13 [get_ports {rdq_n[2]}]     ;# finger 191 (F) DQ44 | VREF_N2 | bank 66 T2L N5 (bitslice 5) | IO_L15N_T2L_N5_AD11N_66 | static reference of rdq_p[2]; never driven by the FPGA
set_property PACKAGE_PIN AF8  [get_ports {rdq_p[3]}]     ;# finger 194 (B) DQ41 | DQ3 (U1.D3) | bank 66 T2U N10 (bitslice 4) | IO_L18P_T2U_N10_AD2P_66 | not matched on the card: total 880.59 ps, -42.53 ps to the strobe
set_property PACKAGE_PIN AG8  [get_ports {rdq_n[3]}]     ;# finger 195 (F) DQ40 | VREF_N3 | bank 66 T2U N11 (bitslice 5) | IO_L18N_T2U_N11_AD2N_66 | static reference of rdq_p[3]; never driven by the FPGA
set_property PACKAGE_PIN AJ9  [get_ports {rdq_p[4]}]     ;# finger 215 (F) DQ49 | DQ4 (U1.B5) | bank 66 T1U N10 (bitslice 4) GC | IO_L12P_T1U_N10_GC_66 | not matched on the card: total 949.67 ps, +26.56 ps to the strobe
set_property PACKAGE_PIN AK9  [get_ports {rdq_n[4]}]     ;# finger 216 (B) DQ48 | VREF_N4 | bank 66 T1U N11 (bitslice 5) GC | IO_L12N_T1U_N11_GC_66 | static reference of rdq_p[4]; never driven by the FPGA
set_property PACKAGE_PIN AK12 [get_ports {rdq_p[5]}]     ;# finger 212 (B) DQ53 | DQ5 (U1.C6) | bank 66 T1L N4 (bitslice 4) | IO_L9P_T1L_N4_AD12P_66 | not matched on the card: total 946.18 ps, +23.06 ps to the strobe
set_property PACKAGE_PIN AL12 [get_ports {rdq_n[5]}]     ;# finger 211 (F) DQ52 | VREF_N5 | bank 66 T1L N5 (bitslice 5) | IO_L9N_T1L_N5_AD12N_66 | static reference of rdq_p[5]; never driven by the FPGA
set_property PACKAGE_PIN AE12 [get_ports {rdq_p[6]}]     ;# finger 186 (B) DQ35 | DQ6 (U1.E6) | bank 66 T3U N8 (bitslice 2) | IO_L23P_T3U_N8_66 | not matched on the card: total 844.38 ps, -78.74 ps to the strobe
set_property PACKAGE_PIN AF12 [get_ports {rdq_n[6]}]     ;# finger 187 (F) DQ34 | VREF_N6 | bank 66 T3U N9 (bitslice 3) | IO_L23N_T3U_N9_66 | static reference of rdq_p[6]; never driven by the FPGA
set_property PACKAGE_PIN AD14 [get_ports {rdq_p[7]}]     ;# finger 182 (B) DQ39 | DQ7 (U1.F5) | bank 66 T3L N2 (bitslice 2) | IO_L20P_T3L_N2_AD1P_66 | not matched on the card: total 835.98 ps, -87.13 ps to the strobe
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
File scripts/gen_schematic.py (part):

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

def ball_name(b):
    """JEDEC pin function without the ball suffix: 'CA0_A_G4' -> 'CA0_A'."""
    f = BALLS[b]["pin_function"]
    assert f.endswith("_" + b), (b, f)
    return f[:-len(b) - 1]
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    vdd, spd, i2c, gnd, nc = of("VDD"), of("VDDSPD"), of("I2C"), of("VSS"), of("no")
    assert len(cmd) == 10 and len(wr) == 10 and len(rst) == 1 and len(rd) == 18 and len(i2c) == 2
    assert all(pins[str(n)] == "GND" for n in gnd) and all(pins[str(n)] == "" for n in nc)
    assert all(pins[str(n)] == "V1P2" for n in vdd) and pins[str(spd[0])] == "V3P3"
    assert len(cmd + wr + rst + rd + vdd + spd + i2c + gnd + nc) == 260
    half = (len(nc) + 1) // 2
    ghalf = len(gnd) // 2
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

def pair_text(t_net, c_net, inverted=False):
    """'CK_P on finger 76 (P pin), CK_N on finger 74 (N pin)' from the finger table (finger-side nets).
    inverted: the true leg is on the N pin of the host pair and the complement on the P pin (the gateware drives the
    pair inverted); the text says so."""
    out = []
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    note(sh, "Levels at the ball (min / nominal / max)", 259.08, 43.18, size=1.5, bold=True)
    note(sh,
         "Corners: %s.\n\n"
         "CA0-6, CK_P, CK_N:  %d R / %d R   %.3f / %.3f / %.3f V   pin current %.1f mA max\n"
         "    back impedance %.1f ohm into the %.1f ohm In3 line; limit: %s\n\n"
         "CS0:  %d R / %d R   %.3f / %.3f / %.3f V   pin current %.1f mA max\n"
         "    limit: %s\n\n"
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
    # --- RDQS --------------------------------------------------------------------------------
    rdqs = [(n, next(r for r in here if netof(r, 1) == n and netof(r, 2) == "GND")) for n in ("RDQS_P", "RDQS_N")]
    note(sh, "RDQS: %s load per leg, no series part; host pair DQS6 (fingers 219 / 221) inverted (RDQS_P on its N pin)" % rtxt(same_value(r[1] for r in rdqs)),
         25.4, 151.13, size=1.5, bold=True)
    for i, (n, load) in enumerate(rdqs):
        x, y = 40.64, 165.1 + i * 30.48
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        sh.wire(a, b)
    for p in line[:-1]:
        sh.junction(*p)
    sh.glabel("VREF_RD", xend, yv, (1, 0))
    sh.wire(pt(r331, 2), (x331, yv))
    sh.wire(pt(r332, 2), (x332, yv))
    power(sh, netof("R332", 1), *pt(r332, 1))
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    sh.junction(xj, yo)
    sh.junction(xj, fb[1])
    sh.wire((xj, fb[1]), (xj + P, fb[1]))
    sh.glabel("DAC_OUT", xj + P, fb[1], (1, 0))
    cap = pt(u5, 4)                                   # CAP -> C333 -> GND
    c333 = place_c(sh, "C333", cap[0] + 7.62, cap[1] + 6.35)
    sh.wire(cap, (cap[0] + 7.62, cap[1]), pt(c333, 1))
    sh.wire((cap[0] + 7.62, cap[1]), (cap[0] + 12.7, cap[1]))
    sh.junction(cap[0] + 7.62, cap[1])
    sh.glabel("DAC_CAP", cap[0] + 12.7, cap[1], (1, 0))
    power(sh, "GND", *pt(c333, 2))
    vdd = pt(u5, 6)                                   # VDD, decoupled by C332
    vtop = (vdd[0], vdd[1] - 5.08)
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    sh.wire(en, (corner[0], en[1]), corner, pt(r504, 2))
    sh.wire(corner, (corner[0] + P, ye))
    sh.junction(*corner)
    sh.glabel("PWR_EN", corner[0] + P, ye, (1, 0))
    v1 = (en[0] - 25.4, ye)
    sh.wire(pt(r504, 1), v1)
    power(sh, netof("R504", 1), *v1)
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    assert netof("R503", 2) == netof("U2", 3) == "PG_VDD2H"
    sh.wire(pg, (pg[0] + P, pg[1]), (pg[0] + P, yp), pt(r503, 2), (xr + 5.08, yp))
    sh.junction(xr, yp)
    sh.glabel("PG_VDD2H", xr + 5.08, yp, (1, 0))
    power(sh, netof("R503", 1), *pt(r503, 1))
    note(sh, "VOUT = 0.8 V x (1 + R501 / R502) = %.3f V, %s.\n"
             "EN = %s.  C504 (%s): %.1f ms soft start.  PG (open drain, %s to %s) enables U4.\n%s"
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
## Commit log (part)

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2025-11-04 [#86301] Project refresh 81589
2025-11-04 kmake dnp
